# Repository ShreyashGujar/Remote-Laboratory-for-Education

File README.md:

Project Descriptions: The following are detailed descriptions of the project folders included in this repository.

Cattle Releaser System:
A safety-focused system designed to protect cattle during floods, fires, and other emergencies. The mechanism automatically releases confined cattle, allowing them to move freely and reducing the risk of injury or fatality. The project highlights automated actuation, environmental sensing, and disaster-response engineering.

Microcontroller-Based Timer Switch:
A programmable timer switch developed to control electrical appliances at predefined intervals. The work includes PCB design, firmware development, and a simple user interface for adjusting timing parameters. Key concepts include relay driving, switch debouncing, and stabilizing circuits when interfacing with mains-powered loads.

Warning System for Fog Settlement and Fire:
A dual-purpose environmental safety system designed to protect agricultural fields by detecting fog settlement and early fire indicators. The platform also provides real-time soil-moisture monitoring, enabling farmers to track and manage field conditions on a daily basis.

Construction-Site Pollution Monitoring System:
Low-cost IoT nodes developed for monitoring both indoor and outdoor air pollution around construction sites. The system integrates air-quality sensors, power management, and wireless communication to transmit data to a centralized dashboard. Field deployment involved designing rugged hardware capable of ensuring reliable and stable readings in harsh environments.

IoT-Based AQI Estimation Using Image Processing:
An IoT-enabled real-time AQI estimation system integrating image processing and machine learning to predict air quality levels using traffic imagery and weather-sensor data. The system achieves 82% accuracy through deep learning–based object detection and feature extraction, improving AQI estimation for dense urban areas.

GPS-Enabled Mobile Air Pollution Monitoring System:
A citywide mobile air-quality monitoring solution utilizing GPS-enabled IoT sensors mounted on moving vehicles to measure PM concentrations. The platform supports large-scale spatial and temporal data collection, enabling identification of pollution hotspots and seasonal air-quality variations.

IoT-Based Remote Laboratory Hardware System:
A remotely accessible laboratory hardware platform enabling students to control and observe experiments online. The system includes motor drivers, camera interfaces, and web-controlled actuation mechanisms, supporting demonstrations such as focal-length experiments. This setup enhances access to practical science education for institutions lacking laboratory infrastructure.

AutoBot BLE:
A Bluetooth Low Energy robotic bot developed using the ESP32. The system manages wireless communication, motor control, and real-time execution of directional commands. The project emphasizes low-latency embedded control, motor-noise isolation, and efficient wireless protocol handling.

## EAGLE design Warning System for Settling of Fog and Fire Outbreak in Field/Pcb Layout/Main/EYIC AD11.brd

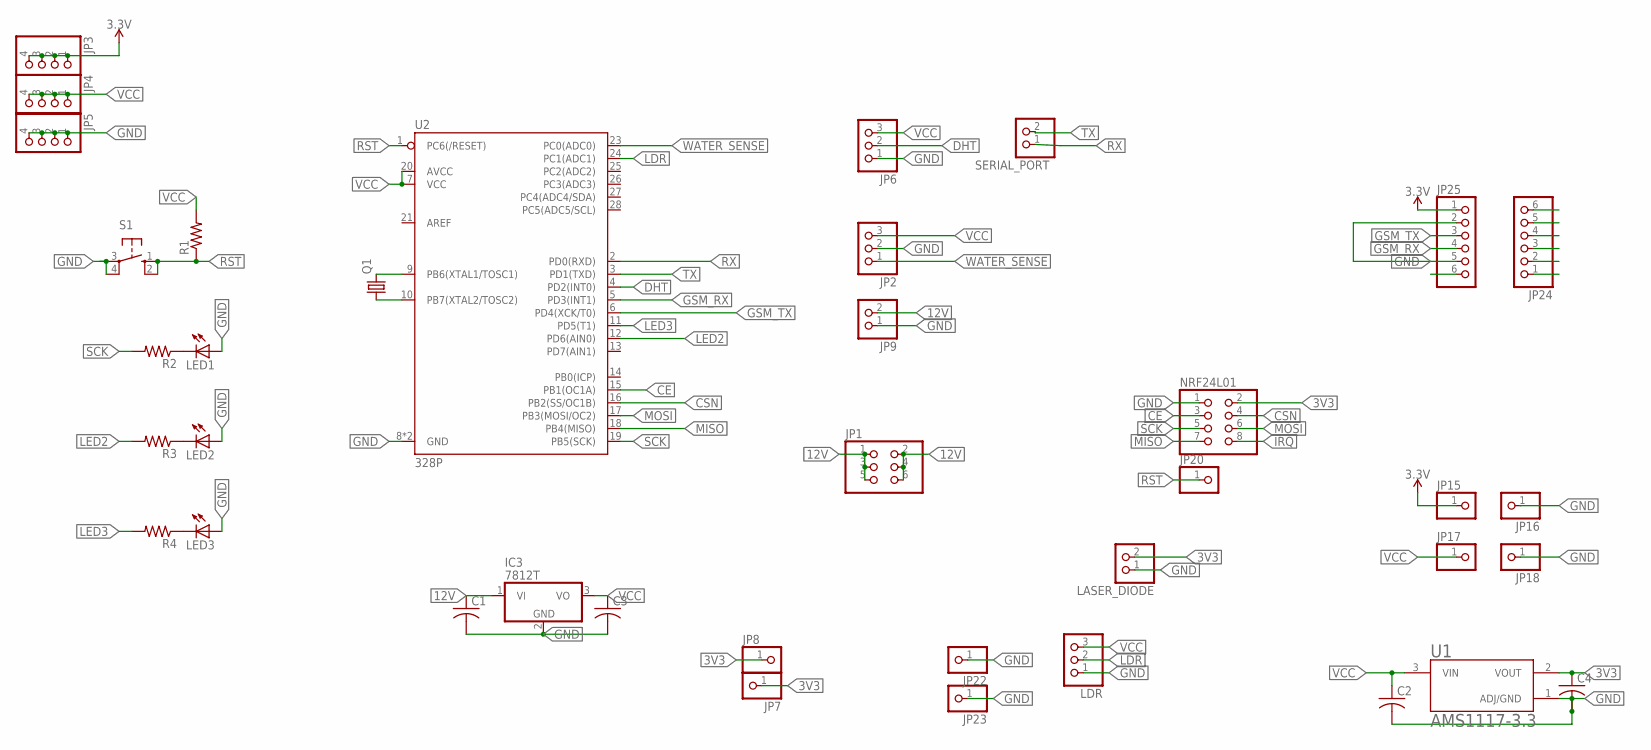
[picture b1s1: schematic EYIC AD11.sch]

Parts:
C1, C3: C-US050-035X075; C050-035X075
C2, C4: C-US025-060X050; C025-060X050
IC3: 7812T; TO220H
JP1: PINHD-2X3; 2X03
JP2, JP6: PINHD-1X3; 1X03
JP3, JP4, JP5: PINHD-1X4; 1X04
JP7, JP8, JP15, JP16, JP17, JP18, JP20, JP22, JP23: PINHD-1X1; 1X01
JP9: PINHD-1X2; 1X02
JP24, JP25: PINHD-1X6; 1X06
LASER_DIODE: PINHD-1X2; 1X02
LDR: PINHD-1X3; 1X03
LED1, LED2, LED3: LED5MM
NRF24L01: PINHD-2X4; 2X04
Q1: CRYSTALHC49S; HC49/S
R1, R2, R3, R4: R-US_0207/7; 0207/7
S1: 10-XX; B3F-10XX
SERIAL_PORT: PINHD-1X2; 1X02
U1: AMS1117-3.3; SOT229P700X180-4N
U2: 328P; DIP28

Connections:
3.3V: JP3.1, JP3.2, JP3.3, JP3.4, JP15.1, JP25.1
3V3: C4.1, JP7.1, JP8.1, LASER_DIODE.2, NRF24L01.2, U1.2 (VOUT)
12V: C1.1, IC3.1 (VI), JP1.1, JP1.2, JP1.3, JP1.4, JP1.5, JP1.6, JP9.2
CE: NRF24L01.3, U2.15 (PB1(OC1A))
CSN: NRF24L01.4, U2.16 (PB2(SS/OC1B))
DHT: JP6.2, U2.4 (PD2(INT0))
GND: C1.2, C2.2, C3.2, C4.2, IC3.2 (GND), JP2.2, JP5.1, JP5.2, JP5.3, JP5.4, JP6.1, JP9.1, JP16.1, JP18.1, JP22.1, JP23.1, JP25.2, JP25.5, LASER_DIODE.1, LDR.1, LED1.A, LED2.A, LED3.A, NRF24L01.1, S1.3, S1.4 (P1), U1.1 (ADJ/GND), U2.8 (GND), U2.22 (GND)
GSM_RX: JP25.4, U2.5 (PD3(INT1))
GSM_TX: JP25.3, U2.6 (PD4(XCK/T0))
IRQ: NRF24L01.8
LDR: LDR.2, U2.24 (PC1(ADC1))
LED2: R3.2, U2.12 (PD6(AIN0))
LED3: R4.2, U2.11 (PD5(T1))
MISO: NRF24L01.7, U2.18 (PB4(MISO))
MOSI: NRF24L01.6, U2.17 (PB3(MOSI/OC2))
unnamed: Q1.2, U2.9 (PB6(XTAL1/TOSC1))
unnamed: Q1.1, U2.10 (PB7(XTAL2/TOSC2))
unnamed: LED1.K (C), R2.1
unnamed: LED2.K (C), R3.1
unnamed: LED3.K (C), R4.1
RST: JP20.1, R1.1, S1.1 (S), S1.2 (S1), U2.1 (PC6(/RESET))
RX: SERIAL_PORT.1, U2.2 (PD0(RXD))
SCK: NRF24L01.5, R2.2, U2.19 (PB5(SCK))
TX: SERIAL_PORT.2, U2.3 (PD1(TXD))
VCC: C2.1, C3.1, IC3.3 (VO), JP2.3, JP4.1, JP4.2, JP4.3, JP4.4, JP6.3, JP17.1, LDR.3, R1.2, U1.3 (VIN), U2.7 (VCC), U2.20 (AVCC)
WATER_SENSE: JP2.1, U2.23 (PC0(ADC0))

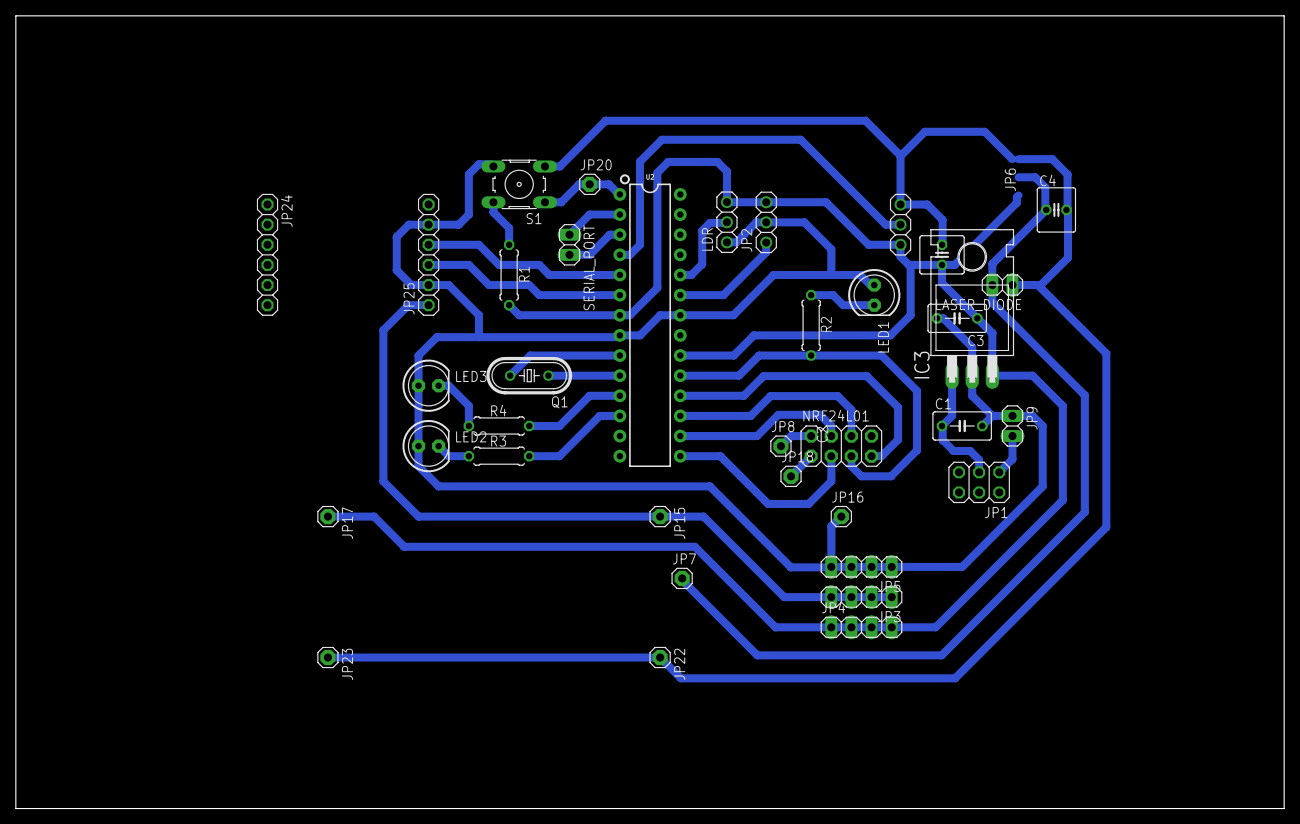
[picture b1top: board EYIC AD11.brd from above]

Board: 2 copper layers, 160.0 x 100.0 mm, 38 parts (1 on the bottom side), 25 nets.

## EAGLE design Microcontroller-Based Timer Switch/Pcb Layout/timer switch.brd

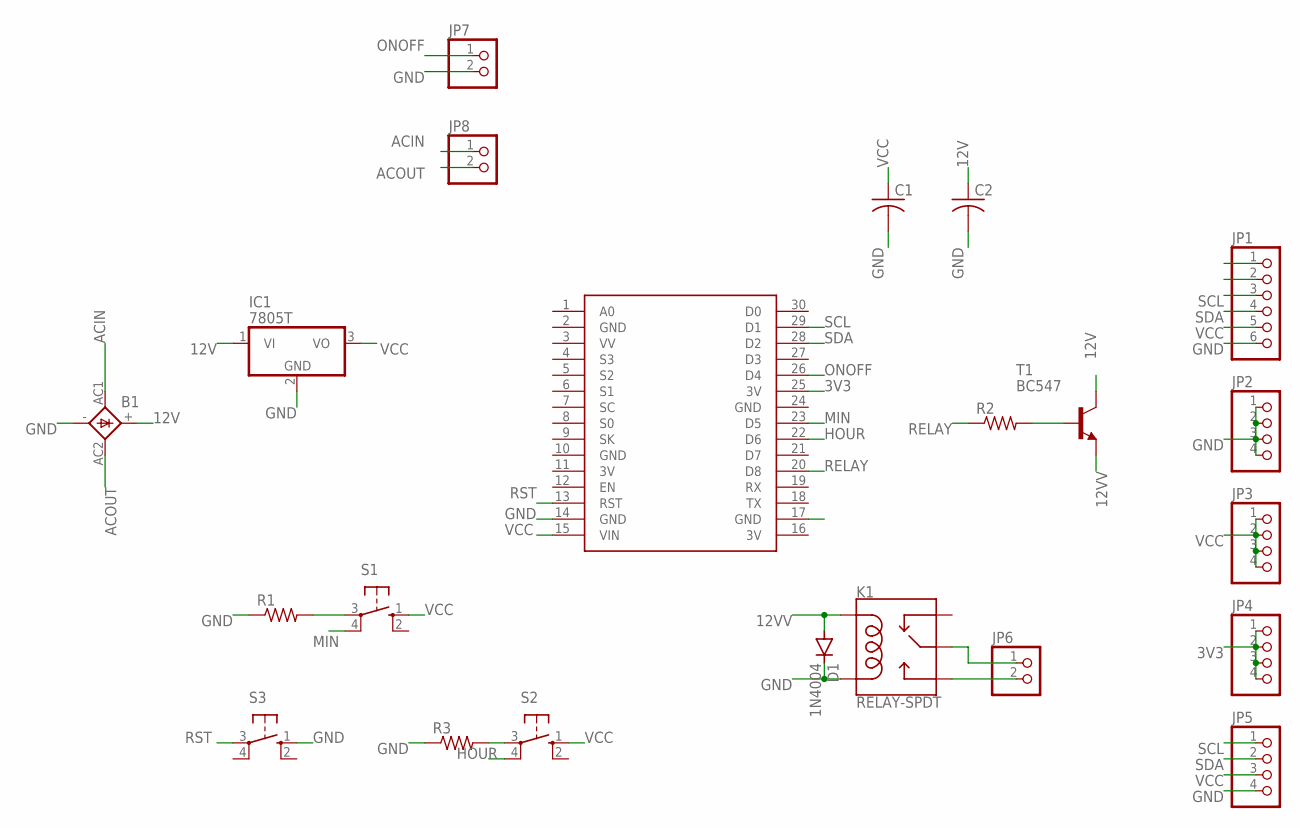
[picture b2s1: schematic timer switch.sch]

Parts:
B1: S41
C1, C2: C-US025-050X050; C025-050X050
D1: 1N4004; DO41-10
IC1: 7805T; TO220H
JP1: PINHD-1X6; 1X06
JP2, JP3, JP4, JP5: PINHD-1X4; 1X04
JP6, JP7, JP8: PINHD-1X2; 1X02
K1: RELAY-SPDT; RELAY_G5LE
R1, R2, R3: R-US_0207/9; 0207/9
S1, S2, S3: 10-XX; B3F-10XX
T1: BC547; TO92
U$1: NODEMCU

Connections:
3V: U$1.11 (3V), U$1.16 (3V)
3V3: JP4.1, JP4.2, JP4.3, JP4.4, U$1.25 (3V)
12V: B1.+, C2.1, IC1.1 (VI), T1.3 (C)
12VV: D1.A, K1.2 (COIL1), T1.1 (E)
ACIN: B1.AC1, JP8.1
ACOUT: B1.AC2, JP8.2
GND: B1.-, C1.2, C2.2, D1.C, IC1.2 (GND), JP1.6, JP2.1, JP2.2, JP2.3, JP2.4, JP5.4, JP7.2, K1.5 (COIL2), R1.1, R3.1, S3.1 (S), U$1.2 (GND), U$1.10 (GND), U$1.14 (GND), U$1.24 (GND)
HOUR: S2.4 (P1), U$1.22 (D6)
MIN: S1.4 (P1), U$1.23 (D5)
unnamed: JP6.1, K1.1 (MAIN)
unnamed: JP6.2, K1.3 (NO)
unnamed: R2.2, T1.2 (B)
unnamed: R1.2, S1.3
unnamed: R3.2, S2.3
ONOFF: JP7.1, U$1.26 (D4)
RELAY: R2.1, U$1.20 (D8)
RST: S3.3, U$1.13 (RST)
SCL: JP1.3, JP5.1, U$1.29 (D1)
SDA: JP1.4, JP5.2, U$1.28 (D2)
VCC: C1.1, IC1.3 (VO), JP1.5, JP3.1, JP3.2, JP3.3, JP3.4, JP5.3, S1.1 (S), S2.1 (S), U$1.15 (VIN)

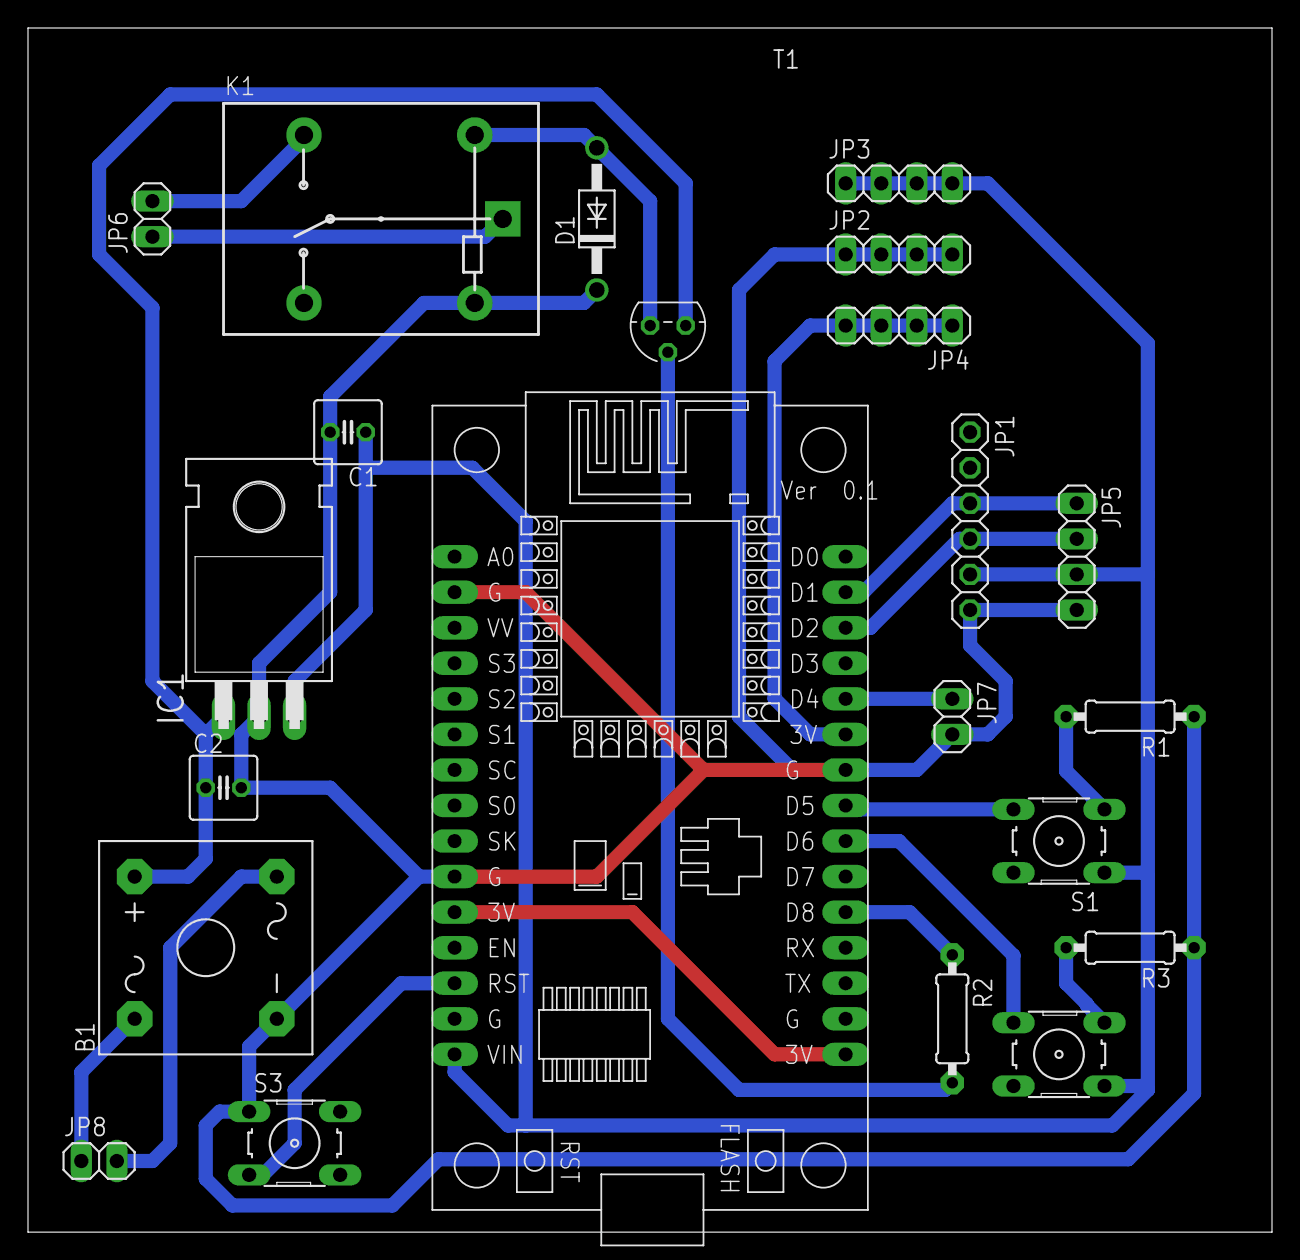
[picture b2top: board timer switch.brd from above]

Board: 2 copper layers, 88.9 x 86.0 mm, 22 parts (0 on the bottom side), 20 nets.

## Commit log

2025-12-11 README.md

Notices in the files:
parts and their libraries:
SparkFun-Electromechanical: Licensing: Creative Commons ShareAlike 4.0 International - https://creativecommons.org/licenses/by-sa/4.0
